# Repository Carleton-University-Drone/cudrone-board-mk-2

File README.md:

# cudrone-board-mk-2
This is the second iteration of the drone's main flight controller. The main processor for this board is an intel edison.

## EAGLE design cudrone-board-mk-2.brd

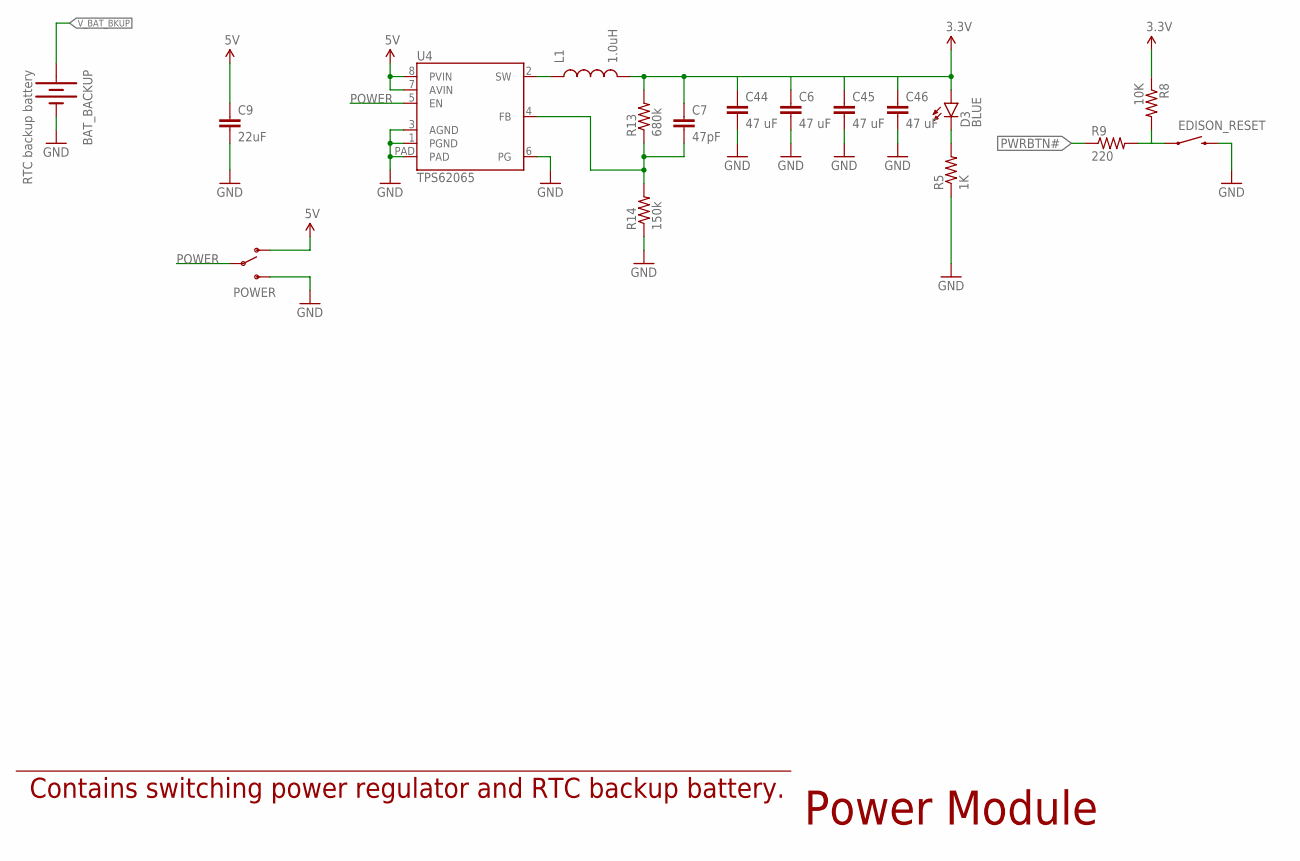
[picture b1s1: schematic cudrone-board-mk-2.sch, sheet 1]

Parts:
BAT_BACKUP: RTC backup battery; BATTCON_12MM
C6, C44, C45, C46: 47 uF; 0805
C7: 47pF; 0603-CAP
C9: 22uF; 0805
D3: BLUE; LED-0603
EDISON_RESET: SWITCH-MOMENTARY-2; EVQPSC02K
L1: 1.0uH; INDUCTOR-SRP4020
POWER: CANSAT_SWITCH; JS102011SAQN-SPDT
R5: 1K; 0603-RES@1
R8: 10K; 0603-RES@1
R9: 220; 0603-RES@1
R13: 680k; 0603-RES
R14: 150k; 0603-RES
U4: TPS62065; WSON-8-PAD

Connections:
3.3V: C6.1, C7.1, C44.1, C45.1, C46.1, D3.A, L1.P$2 (2), R8.1, R13.2; also elsewhere on the board
5V: C9.1, POWER.P$1 (O), U4.7 (AVIN), U4.8 (PVIN); also elsewhere on the board
GND: BAT_BACKUP.GND (-), C6.2, C9.2, C44.2, C45.2, C46.2, EDISON_RESET.B (2), EDISON_RESET.B' (2), POWER.P$3 (S), R5.1, R14.1, U4.1 (PGND), U4.3 (AGND), U4.6 (PG), U4.PAD; also elsewhere on the board
unnamed: D3.C, R5.2
unnamed: EDISON_RESET.A (1), EDISON_RESET.A' (1), R8.2, R9.2
unnamed: C7.2, R13.1, R14.2, U4.4 (FB)
unnamed: L1.P$1 (1), U4.2 (SW)
POWER: POWER.P$C, U4.5 (EN)
PWRBTN#: R9.1; also elsewhere on the board
V_BAT_BKUP: BAT_BACKUP.PWR@1 (+); also elsewhere on the board

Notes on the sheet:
Power Module
Contains switching power regulator and RTC backup battery.

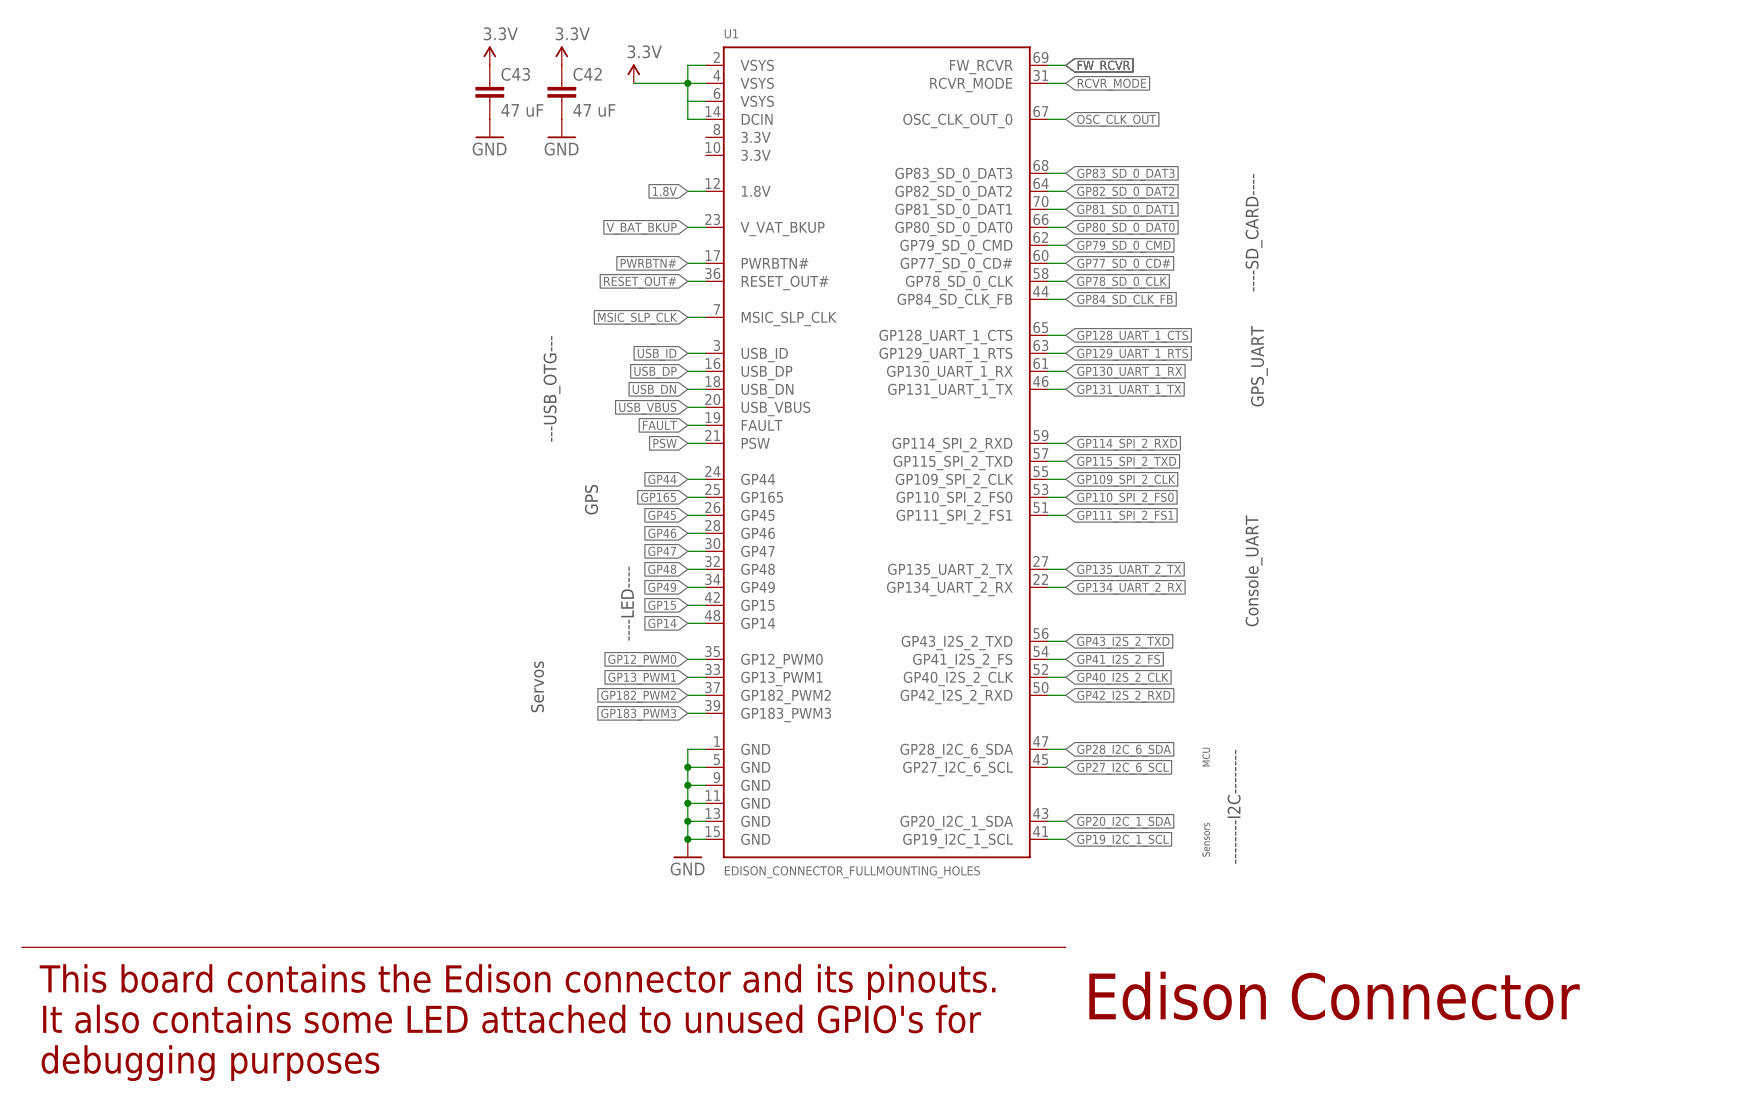
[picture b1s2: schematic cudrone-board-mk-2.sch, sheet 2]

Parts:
C42, C43: 47 uF; 0805
U1: EDISON_CONNECTOR_FULLMOUNTING_HOLES; EDISON_DAUGHTER

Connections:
1.8V: U1.12 (1.8V); also elsewhere on the board
3.3V: C42.1, C43.1, U1.2 (VSYS), U1.4 (VSYS), U1.6 (VSYS), U1.14 (DCIN); also elsewhere on the board
FAULT: U1.19 (FAULT); also elsewhere on the board
FW_RCVR: U1.69 (FW_RCVR)
GND: C42.2, C43.2, U1.1 (GND), U1.5 (GND), U1.9 (GND), U1.11 (GND), U1.13 (GND), U1.15 (GND); also elsewhere on the board
GP12_PWM0: U1.35 (GP12_PWM0); also elsewhere on the board
GP13_PWM1: U1.33 (GP13_PWM1); also elsewhere on the board
GP14: U1.48 (GP14)
GP15: U1.42 (GP15)
GP19_I2C_1_SCL: U1.41 (GP19_I2C_1_SCL); also elsewhere on the board
GP20_I2C_1_SDA: U1.43 (GP20_I2C_1_SDA); also elsewhere on the board
GP27_I2C_6_SCL: U1.45 (GP27_I2C_6_SCL); also elsewhere on the board
GP28_I2C_6_SDA: U1.47 (GP28_I2C_6_SDA); also elsewhere on the board
GP40_I2S_2_CLK: U1.52 (GP40_I2S_2_CLK)
GP41_I2S_2_FS: U1.54 (GP41_I2S_2_FS)
GP42_I2S_2_RXD: U1.50 (GP42_I2S_2_RXD)
GP43_I2S_2_TXD: U1.56 (GP43_I2S_2_TXD)
GP44: U1.24 (GP44); also elsewhere on the board
GP45: U1.26 (GP45); also elsewhere on the board
GP46: U1.28 (GP46)
GP47: U1.30 (GP47)
GP48: U1.32 (GP48)
GP49: U1.34 (GP49)
GP77_SD_0_CD#: U1.60 (GP77_SD_0_CD#); also elsewhere on the board
GP78_SD_0_CLK: U1.58 (GP78_SD_0_CLK); also elsewhere on the board
GP79_SD_0_CMD: U1.62 (GP79_SD_0_CMD); also elsewhere on the board
GP80_SD_0_DAT0: U1.66 (GP80_SD_0_DAT0); also elsewhere on the board
GP81_SD_0_DAT1: U1.70 (GP81_SD_0_DAT1); also elsewhere on the board
GP82_SD_0_DAT2: U1.64 (GP82_SD_0_DAT2); also elsewhere on the board
GP83_SD_0_DAT3: U1.68 (GP83_SD_0_DAT3); also elsewhere on the board
GP84_SD_CLK_FB: U1.44 (GP84_SD_CLK_FB); also elsewhere on the board
GP109_SPI_2_CLK: U1.55 (GP109_SPI_2_CLK)
GP110_SPI_2_FS0: U1.53 (GP110_SPI_2_FS0)
GP111_SPI_2_FS1: U1.51 (GP111_SPI_2_FS1)
GP114_SPI_2_RXD: U1.59 (GP114_SPI_2_RXD)
GP115_SPI_2_TXD: U1.57 (GP115_SPI_2_TXD)
GP128_UART_1_CTS: U1.65 (GP128_UART_1_CTS)
GP129_UART_1_RTS: U1.63 (GP129_UART_1_RTS)
GP130_UART_1_RX: U1.61 (GP130_UART_1_RX); also elsewhere on the board
GP131_UART_1_TX: U1.46 (GP131_UART_1_TX); also elsewhere on the board
GP134_UART_2_RX: U1.22 (GP134_UART_2_RX); also elsewhere on the board
GP135_UART_2_TX: U1.27 (GP135_UART_2_TX); also elsewhere on the board
GP165: U1.25 (GP165); also elsewhere on the board
GP182_PWM2: U1.37 (GP182_PWM2); also elsewhere on the board
GP183_PWM3: U1.39 (GP183_PWM3); also elsewhere on the board
MSIC_SLP_CLK: U1.7 (MSIC_SLP_CLK)
OSC_CLK_OUT: U1.67 (OSC_CLK_OUT_0)
PSW: U1.21 (PSW); also elsewhere on the board
PWRBTN#: U1.17 (PWRBTN#); also elsewhere on the board
RCVR_MODE: U1.31 (RCVR_MODE)
RESET_OUT#: U1.36 (RESET_OUT#)
USB_DN: U1.18 (USB_DN); also elsewhere on the board
USB_DP: U1.16 (USB_DP); also elsewhere on the board
USB_ID: U1.3 (USB_ID); also elsewhere on the board
USB_VBUS: U1.20 (USB_VBUS); also elsewhere on the board
V_BAT_BKUP: U1.23 (V_VAT_BKUP); also elsewhere on the board

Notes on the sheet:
Edison Connector
This board contains the Edison connector and its pinouts. It also contains some LED attached to unused GPIO's for debugging purposes
Servos
GPS
Console_UART
---USB_OTG---
----SD_CARD----
--------I2C--------
GPS_UART
Sensors
MCU
----LED----

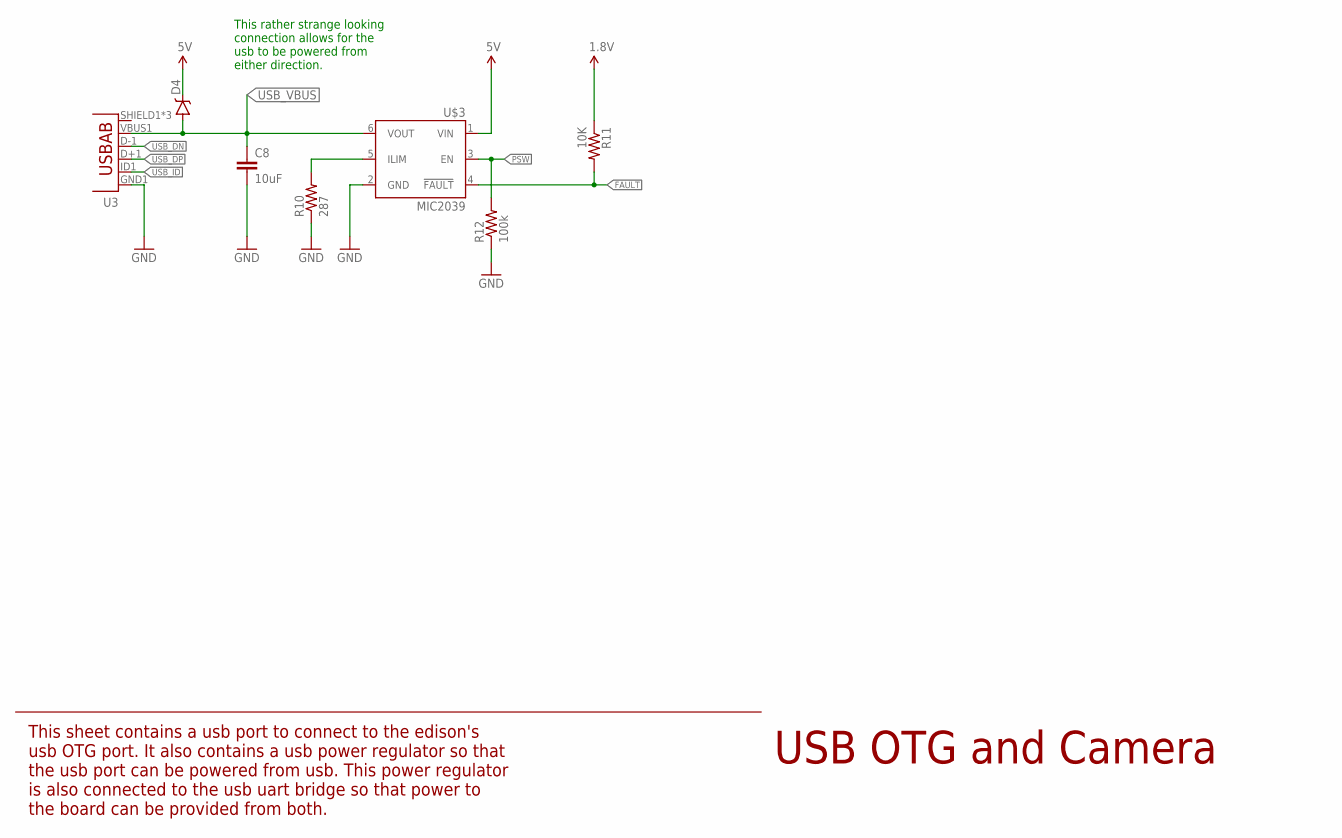
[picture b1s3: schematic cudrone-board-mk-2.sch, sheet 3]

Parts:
C8: 10uF; 1206
D4: DIODE-SCHOTTKY-MBRA140; SMA-DIODE
R10: 287; 0603-RES@1
R11: 10K; 0603-RES@1
R12: 100k; 0603-RES@1
U3: USB-ABCONN-11794; USB-AB-MICRO-SMD_V03
U$3: MIC2039; SOT23-6

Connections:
1.8V: R11.1; also elsewhere on the board
5V: D4.C, U$3.1 (VIN); also elsewhere on the board
FAULT: R11.2, U$3.4 (!FAULT); also elsewhere on the board
GND: C8.2, R10.1, R12.1, U3.GND1 (GND), U$3.2 (GND); also elsewhere on the board
unnamed: R10.2, U$3.5 (ILIM)
PSW: R12.2, U$3.3 (EN); also elsewhere on the board
USB_DN: U3.D-1 (D-); also elsewhere on the board
USB_DP: U3.D+1 (D+); also elsewhere on the board
USB_ID: U3.ID1 (USBID); also elsewhere on the board
USB_VBUS: C8.1, D4.A, U3.VBUS1 (VBUS), U$3.6 (VOUT); also elsewhere on the board

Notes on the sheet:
USB OTG and Camera
This sheet contains a usb port to connect to the edison's usb OTG port. It also contains a usb power regulator so that the usb port can be powered from usb. This power regulator is also connected to the usb uart bridge so that power to the board can be provided from both.
This rather strange looking connection allows for the usb to be powered from either direction.

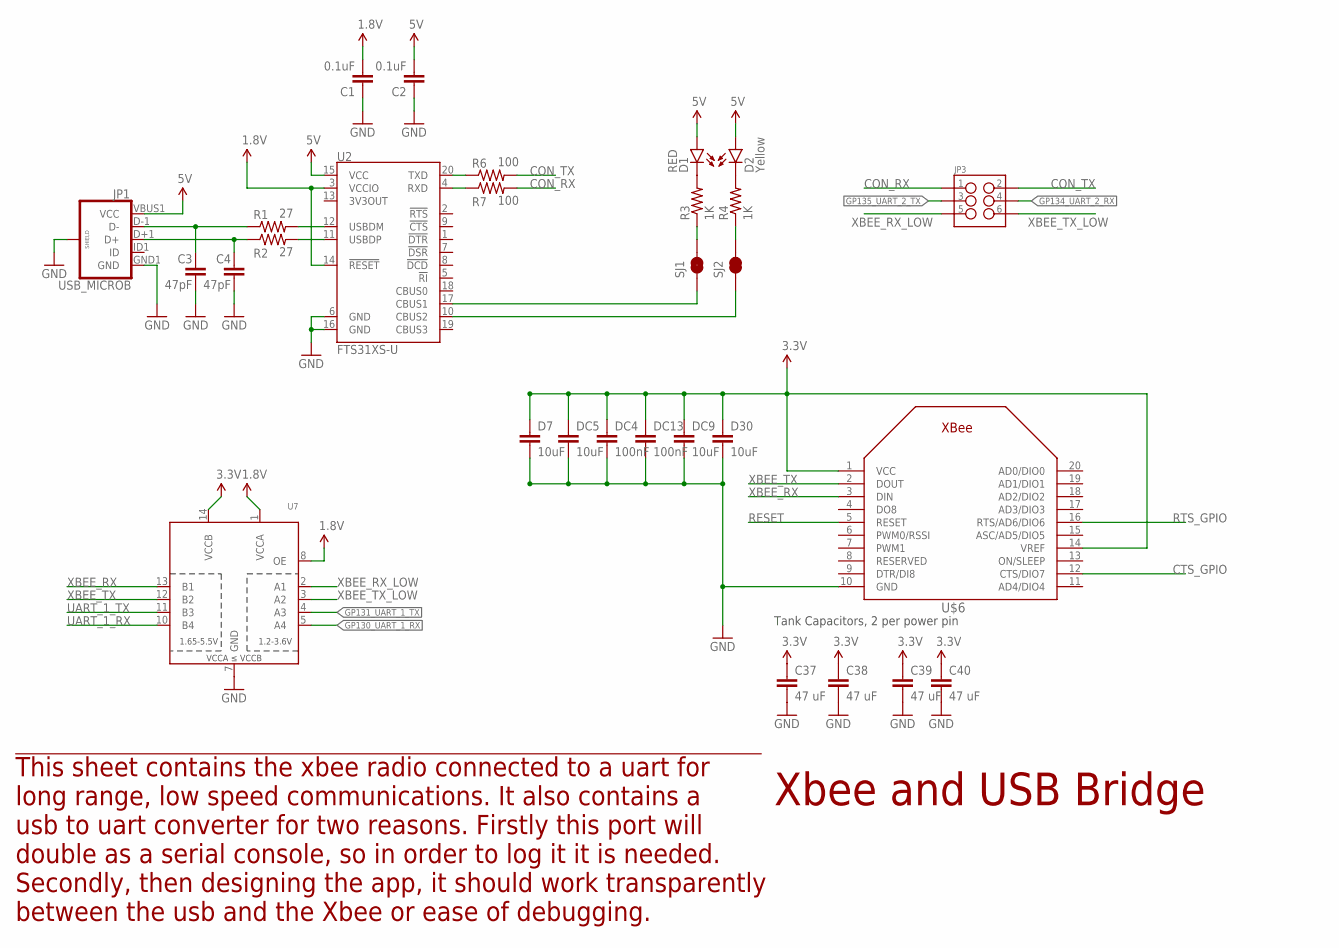
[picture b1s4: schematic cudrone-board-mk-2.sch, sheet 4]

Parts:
C1, C2: 0.1uF; 0603-CAP
C3, C4: 47pF; 0603-CAP
C37, C38, C39, C40: 47 uF; 0805
D1: RED; LED-0603
D2: Yellow; LED-0603
D7, D30: 10uF; 0603-CAP
DC4, DC13: 100nF; 0603-CAP
DC5, DC9: 10uF; 0603-CAP
JP1: USB_MICROB; USB-B-MICRO-SMD_V03
JP3: M03X2DOUBLE_JUMPER_SWAP; 2X3-DOUBLE-JUMPER-SWAP
R1, R2: 27; 0603
R3, R4: 1K; 0603-RES@1
R6, R7: 100; 0603-RES@1
SJ1, SJ2: JUMPER-PAD-2-NC_BY_TRACE; PAD-JUMPER-2-NC_BY_TRACE_YES_SILK
U2: FTS31XS-U; SSOP20_L
U7: TXB0104PWRSOIC14; SO14
U$6: XBEE

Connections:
1.8V: C1.2, U2.3 (VCCIO), U2.14 (!RESET), U7.1 (VCCA), U7.8 (OE); also elsewhere on the board
3.3V: C37.1, C38.1, C39.1, C40.1, D7.1, D30.1, DC4.1, DC5.1, DC9.1, DC13.1, U7.14 (VCCB), U$6.1 (VCC), U$6.14 (VREF); also elsewhere on the board
5V: C2.2, D1.A, D2.A, JP1.VBUS1 (VCC), U2.15 (VCC); also elsewhere on the board
CON_RX: JP3.1, R7.2
CON_TX: JP3.2, R6.2
CTS_GPIO: U$6.12 (CTS/DIO7)
GND: C1.1, C2.1, C3.2, C4.2, C37.2, C38.2, C39.2, C40.2, D7.2, D30.2, DC4.2, DC5.2, DC9.2, DC13.2, JP1.GND1 (GND), JP1.SHIELD1 (SHIELD), JP1.SHIELD2 (SHIELD), JP1.SHIELD3 (SHIELD), U2.6 (GND), U2.16 (GND), U7.7 (GND), U$6.10 (GND); also elsewhere on the board
GP130_UART_1_RX: U7.5 (A4); also elsewhere on the board
GP131_UART_1_TX: U7.4 (A3); also elsewhere on the board
GP134_UART_2_RX: JP3.4; also elsewhere on the board
GP135_UART_2_TX: JP3.3; also elsewhere on the board
unnamed: SJ1.1, U2.17 (CBUS1)
unnamed: C3.1, JP1.D-1 (D-), R1.1
unnamed: C4.1, JP1.D+1 (D+), R2.1
unnamed: R1.2, U2.12 (USBDM)
unnamed: R2.2, U2.11 (USBDP)
unnamed: SJ2.1, U2.10 (CBUS2)
unnamed: R3.1, SJ1.2
unnamed: R4.1, SJ2.2
unnamed: D1.C, R3.2
unnamed: D2.C, R4.2
unnamed: R6.1, U2.20 (TXD)
unnamed: R7.1, U2.4 (RXD)
RESET: U$6.5 (RESET)
RTS_GPIO: U$6.16 (RTS/AD6/DIO6)
UART_1_RX: U7.10 (B4)
UART_1_TX: U7.11 (B3); also elsewhere on the board
XBEE_RX: U7.13 (B1), U$6.3 (DIN)
XBEE_RX_LOW: JP3.5, U7.2 (A1)
XBEE_TX: U7.12 (B2), U$6.2 (DOUT)
XBEE_TX_LOW: JP3.6, U7.3 (A2)

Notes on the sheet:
Xbee and USB Bridge
This sheet contains the xbee radio connected to a uart for long range, low speed communications. It also contains a usb to uart converter for two reasons. Firstly this port will double as a serial console, so in order to log it it is needed. Secondly, then designing the app, it should work transpar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
Tank Capacitors, 2 per power pin

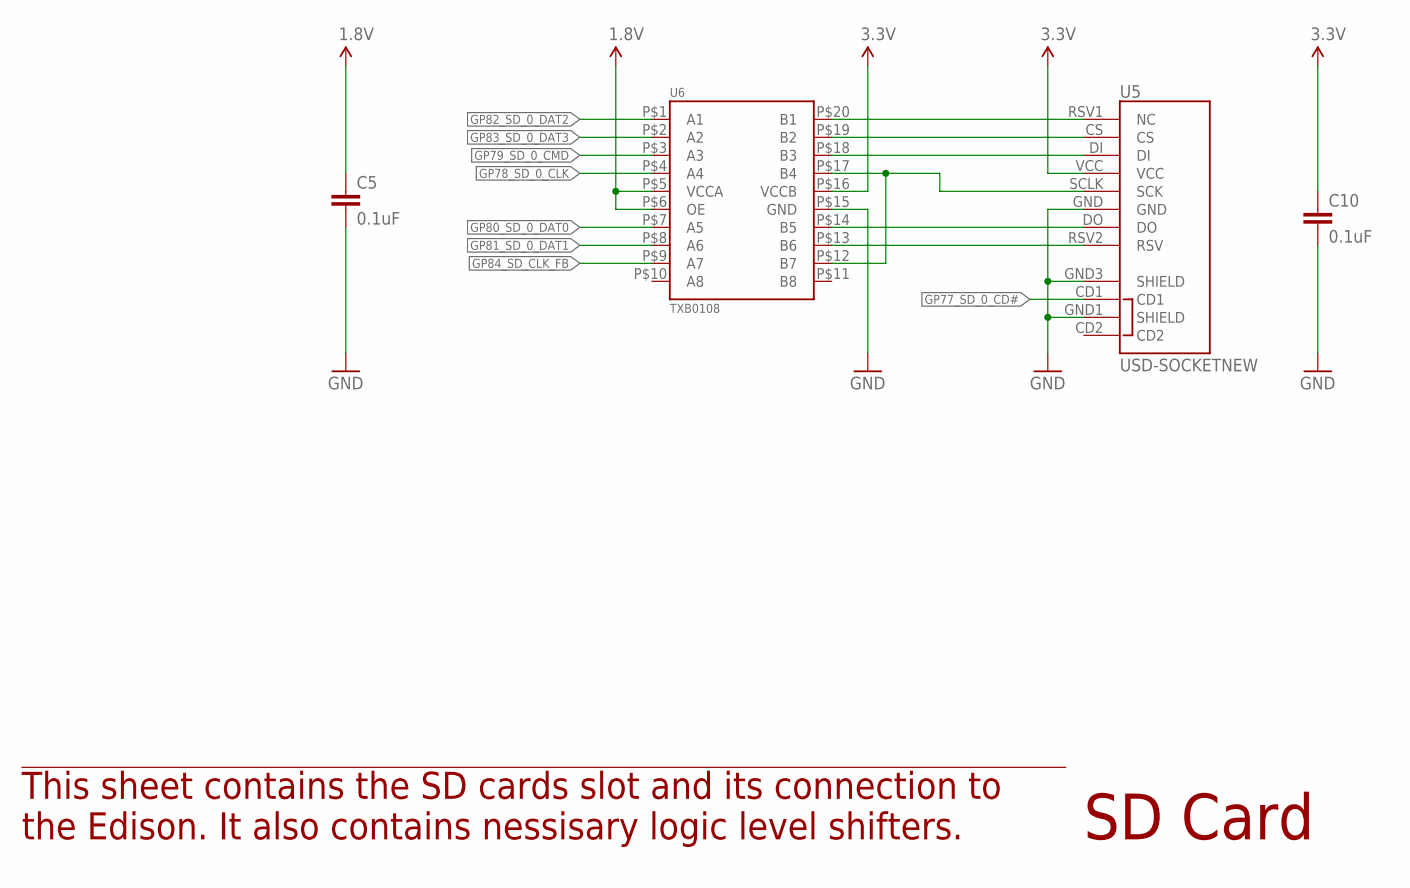
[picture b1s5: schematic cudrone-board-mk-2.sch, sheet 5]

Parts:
C5, C10: 0.1uF; 0603-CAP
U5: USD-SOCKETNEW; MICRO-SD-SOCKET-PP
U6: TXB0108; UFDFN-20

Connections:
1.8V: C5.1, U6.P$5 (VCCA), U6.P$6 (OE); also elsewhere on the board
3.3V: C10.1, U5.VCC, U6.P$16 (VCCB); also elsewhere on the board
GND: C5.2, C10.2, U5.GND, U5.GND1 (SHIELD), U5.GND3 (SHIELD), U6.P$15 (GND); also elsewhere on the board
GP77_SD_0_CD#: U5.CD1; also elsewhere on the board
GP78_SD_0_CLK: U6.P$4 (A4); also elsewhere on the board
GP79_SD_0_CMD: U6.P$3 (A3); also elsewhere on the board
GP80_SD_0_DAT0: U6.P$7 (A5); also elsewhere on the board
GP81_SD_0_DAT1: U6.P$8 (A6); also elsewhere on the board
GP82_SD_0_DAT2: U6.P$1 (A1); also elsewhere on the board
GP83_SD_0_DAT3: U6.P$2 (A2); also elsewhere on the board
GP84_SD_CLK_FB: U6.P$9 (A7); also elsewhere on the board
unnamed: U5.RSV1 (NC), U6.P$20 (B1)
unnamed: U5.CS, U6.P$19 (B2)
unnamed: U5.DI, U6.P$18 (B3)
unnamed: U5.DO, U6.P$14 (B5)
unnamed: U5.RSV2 (RSV), U6.P$13 (B6)
SCK: U5.SCLK (SCK), U6.P$12 (B7), U6.P$17 (B4)

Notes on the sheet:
SD Card
This sheet contains the SD cards slot and its connection to the Edison. It also contains nessisary logic level shifters.

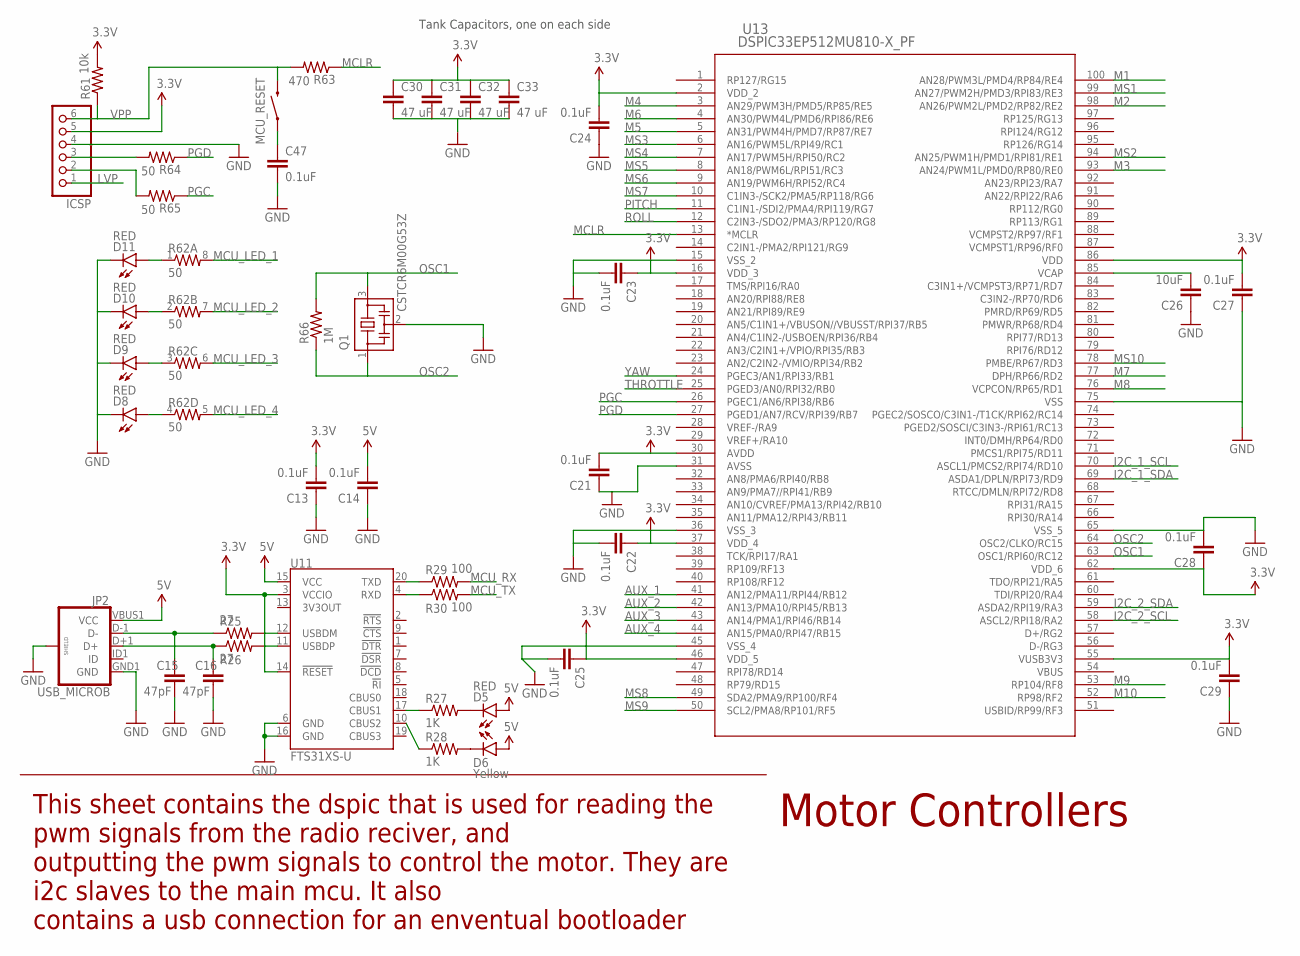
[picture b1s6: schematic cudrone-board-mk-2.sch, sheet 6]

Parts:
C13, C14, C21, C22, C23, C24, C25, C27, C28, C29, C47: 0.1uF; 0603-CAP
C15, C16: 47pF; 0603-CAP
C26: 10uF; 0603-CAP
C30, C31, C32, C33: 47 uF; 0805
D5, D8, D9, D10, D11: RED; LED-0603
D6: Yellow; LED-0603
ICSP: PINHD-1X6/90; 1X06/90
JP2: USB_MICROB; USB-B-MICRO-SMD_V03
MCU_RESET: SWITCH-MOMENTARY-2; EVQPSC02K
Q1: CSTCR6M00G53Z; CSTCR6M
R25, R26: 27; 0603
R27, R28: 1K; 0603-RES@1
R29, R30: 100; 0603-RES@1
R61: 10k; 0603
R62: 50; 0603-ARV
R63: 470; 0603
R64, R65: 50; 0603
R66: 1M; 0603
U11: FTS31XS-U; SSOP20_L
U13: DSPIC33EP512MU810-X_PF; TQFP100_14X14MC

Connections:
3.3V: C13.2, C21.2, C22.1, C23.1, C24.2, C25.1, C27.2, C28.1, C29.2, C30.1, C31.1, C32.1, C33.1, ICSP.5, R61.2, U11.3 (VCCIO), U11.14 (!RESET), U13.2 (VDD_2), U13.16 (VDD_3), U13.30 (AVDD), U13.37 (VDD_4), U13.46 (VDD_5), U13.55 (VUSB3V3), U13.62 (VDD_6), U13.86 (VDD); also elsewhere on the board
5V: C14.2, D5.A, D6.A, JP2.VBUS1 (VCC), U11.15 (VCC); also elsewhere on the board
AUX_1: U13.41 (AN12/PMA11/RPI44/RB12); also elsewhere on the board
AUX_2: U13.42 (AN13/PMA10/RPI45/RB13); also elsewhere on the board
AUX_3: U13.43 (AN14/PMA1/RPI46/RB14); also elsewhere on the board
AUX_4: U13.44 (AN15/PMA0/RPI47/RB15); also elsewhere on the board
GND: C13.1, C14.1, C15.2, C16.2, C21.1, C22.2, C23.2, C24.1, C25.2, C26.1, C27.1, C28.2, C29.1, C30.2, C31.2, C32.2, C33.2, C47.2, D8.C, D9.C, D10.C, D11.C, ICSP.4, JP2.GND1 (GND), JP2.SHIELD1 (SHIELD), JP2.SHIELD2 (SHIELD), JP2.SHIELD3 (SHIELD), Q1.2, U11.6 (GND), U11.16 (GND), U13.15 (VSS_2), U13.31 (AVSS), U13.36 (VSS_3), U13.45 (VSS_4), U13.65 (VSS_5), U13.75 (VSS); also elsewhere on the board
I2C_1_SCL: U13.70 (ASCL1/PMCS2/RPI74/RD10); also elsewhere on the board
I2C_1_SDA: U13.69 (ASDA1/DPLN/RPI73/RD9); also elsewhere on the board
I2C_2_SCL: U13.58 (ASCL2/RPI18/RA2); also elsewhere on the board
I2C_2_SDA: U13.59 (ASDA2/RPI19/RA3); also elsewhere on the board
LVP: ICSP.1
M1: U13.100 (AN28/PWM3L/PMD4/RP84/RE4); also elsewhere on the board
M2: U13.98 (AN26/PWM2L/PMD2/RP82/RE2); also elsewhere on the board
M3: U13.93 (AN24/PWM1L/PMD0/RP80/RE0); also elsewhere on the board
M4: U13.3 (AN29/PWM3H/PMD5/RP85/RE5); also elsewhere on the board
M5: U13.5 (AN31/PWM4H/PMD7/RP87/RE7); also elsewhere on the board
M6: U13.4 (AN30/PWM4L/PMD6/RPI86/RE6); also elsewhere on the board
M7: U13.77 (DPH/RP66/RD2); also elsewhere on the board
M8: U13.76 (VCPCON/RP65/RD1); also elsewhere on the board
M9: U13.53 (RP104/RF8); also elsewhere on the board
M10: U13.52 (RP98/RF2); also elsewhere on the board
MCLR: R63.1, U13.13 (*MCLR)
MCU_LED_1: R62.8 (2)
MCU_LED_2: R62.7 (2)
MCU_LED_3: R62.6 (2)
MCU_LED_4: R62.5 (2)
MCU_RX: R29.2
MCU_TX: R30.2
MS1: U13.99 (AN27/PWM2H/PMD3/RPI83/RE3); also elsewhere on the board
MS2: U13.94 (AN25/PWM1H/PMD1/RPI81/RE1); also elsewhere on the board
MS3: U13.6 (AN16/PWM5L/RPI49/RC1); also elsewhere on the board
MS4: U13.7 (AN17/PWM5H/RPI50/RC2); also elsewhere on the board
MS5: U13.8 (AN18/PWM6L/RPI51/RC3); also elsewhere on the board
MS6: U13.9 (AN19/PWM6H/RPI52/RC4); also elsewhere on the board
MS7: U13.10 (C1IN3-/SCK2/PMA5/RP118/RG6); also elsewhere on the board
MS8: U13.49 (SDA2/PMA9/RP100/RF4); also elsewhere on the board
MS9: U13.50 (SCL2/PMA8/RP101/RF5); also elsewhere on the board
MS10: U13.78 (PMBE/RP67/RD3); also elsewhere on the board
unnamed: D8.A, R62.4 (1)
unnamed: C15.1, JP2.D-1 (D-), R25.1
unnamed: C16.1, JP2.D+1 (D+), R26.1
unnamed: R25.2, U11.12 (USBDM)
unnamed: R26.2, U11.11 (USBDP)
unnamed: C26.2, U13.85 (VCAP)
unnamed: R28.1, U11.10 (CBUS2)
unnamed: R27.1, U11.17 (CBUS1)
unnamed: D9.A, R62.3 (1)
unnamed: D5.C, R27.2
unnamed: D6.C, R28.2
unnamed: R29.1, U11.20 (TXD)
unnamed: R30.1, U11.4 (RXD)
unnamed: D10.A, R62.2 (1)
unnamed: D11.A, R62.1
unnamed: C47.1, MCU_RESET.A (1), MCU_RESET.A' (1)
unnamed: ICSP.3, R64.2
unnamed: ICSP.2, R65.2
OSC1: Q1.3, R66.2, U13.63 (OSC1/RPI60/RC12)
OSC2: Q1.1, R66.1, U13.64 (OSC2/CLKO/RC15)
PGC: R65.1, U13.26 (PGEC1/AN6/RPI38/RB6)
PGD: R64.1, U13.27 (PGED1/AN7/RCV/RPI39/RB7)
PITCH: U13.11 (C1IN1-/SDI2/PMA4/RPI119/RG7); also elsewhere on the board
ROLL: U13.12 (C2IN3-/SDO2/PMA3/RP120/RG8); also elsewhere on the board
THROTTLE: U13.25 (PGED3/AN0/RPI32/RB0); also elsewhere on the board
VBUS: U13.54 (VBUS)
VPP: ICSP.6, MCU_RESET.B (2), MCU_RESET.B' (2), R61.1, R63.2
YAW: U13.24 (PGEC3/AN1/RPI33/RB1); also elsewhere on the board

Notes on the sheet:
Motor Controllers
This sheet contains the dspic that is used for reading the pwm signals from the radio reciver, and outputting the pwm signals to control the motor. They are i2c slaves to the main mcu. It also contains a usb connection for an enventual bootloader
Tank Capacitors, one on each side

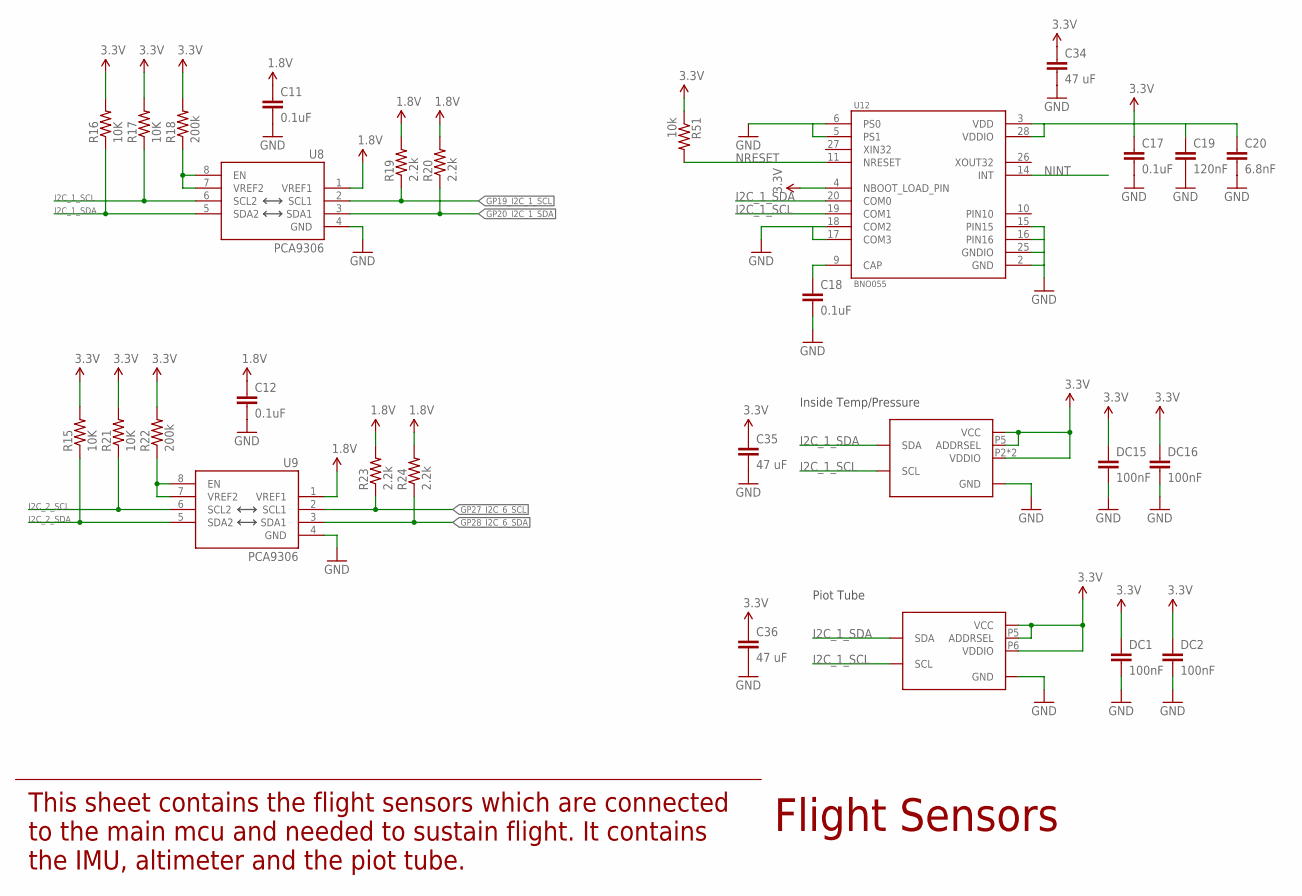
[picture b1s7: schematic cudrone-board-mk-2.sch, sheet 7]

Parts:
C11, C12, C17, C18: 0.1uF; 0603-CAP
C19: 120nF; 0603-CAP
C20: 6.8nF; 0603-CAP
C34, C35, C36: 47 uF; 0805
DC1, DC2, DC15, DC16: 100nF; 0603-CAP
R15, R16, R17, R21: 10K; 0603-RES@1
R18, R22: 200k; 0603-RES@1
R19, R20, R23, R24: 2.2k; 0603-RES@1
R51: 10k; 0805
U8, U9: PCA9306; PCA9306DC-1:1
U12: BNO055; LGA28R50P4X10_380X520X100
U$4: BMP280; LGA-8
U$5: BMP280PITOT; BMP280_PITOT

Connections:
1.8V: C11.1, C12.1, R19.2, R20.2, R23.2, R24.2, U8.1 (VREF1), U9.1 (VREF1); also elsewhere on the board
3.3V: C17.1, C19.1, C20.1, C34.1, C35.1, C36.1, DC1.1, DC2.1, DC15.1, DC16.1, R15.2, R16.2, R17.2, R18.2, R21.2, R22.2, R51.1, U12.3 (VDD), U12.4 (NBOOT_LOAD_PIN), U12.28 (VDDIO), U$4.P2 (VDDIO), U$4.P5 (ADDRSEL), U$4.P6 (VDDIO), U$4.P8 (VCC), U$5.P2 (VCC), U$5.P5 (ADDRSEL), U$5.P6 (VDDIO), U$5.P8 (VCC); also elsewhere on the board
GND: C11.2, C12.2, C17.2, C18.2, C19.2, C20.2, C34.2, C35.2, C36.2, DC1.2, DC2.2, DC15.2, DC16.2, U8.4 (GND), U9.4 (GND), U12.2 (GND), U12.5 (PS1), U12.6 (PS0), U12.15 (PIN15), U12.16 (PIN16), U12.17 (COM3), U12.18 (COM2), U12.25 (GNDIO), U$4.P1 (GND), U$4.P7 (GND), U$5.P1 (GND), U$5.P7 (GND); also elsewhere on the board
GP19_I2C_1_SCL: R19.1, U8.2 (SCL1); also elsewhere on the board
GP20_I2C_1_SDA: R20.1, U8.3 (SDA1); also elsewhere on the board
GP27_I2C_6_SCL: R23.1, U9.2 (SCL1); also elsewhere on the board
GP28_I2C_6_SDA: R24.1, U9.3 (SDA1); also elsewhere on the board
I2C_1_SCL: R17.1, U8.6 (SCL2), U12.19 (COM1), U$4.P4 (SCL), U$5.P4 (SCL); also elsewhere on the board
I2C_1_SDA: R16.1, U8.5 (SDA2), U12.20 (COM0), U$4.P3 (SDA), U$5.P3 (SDA); also elsewhere on the board
I2C_2_SCL: R21.1, U9.6 (SCL2); also elsewhere on the board
I2C_2_SDA: R15.1, U9.5 (SDA2); also elsewhere on the board
unnamed: R22.1, U9.7 (VREF2), U9.8 (EN)
unnamed: R18.1, U8.7 (VREF2), U8.8 (EN)
unnamed: C18.1, U12.9 (CAP)
NINT: U12.14 (INT)
NRESET: R51.2, U12.11 (NRESET)
PIN10: U12.10 (PIN10)

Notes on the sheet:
Flight Sensors
This sheet contains the flight sensors which are connected to the main mcu and needed to sustain flight. It contains the IMU, altimeter and the piot tube.
Inside Temp/Pressure
Piot Tube

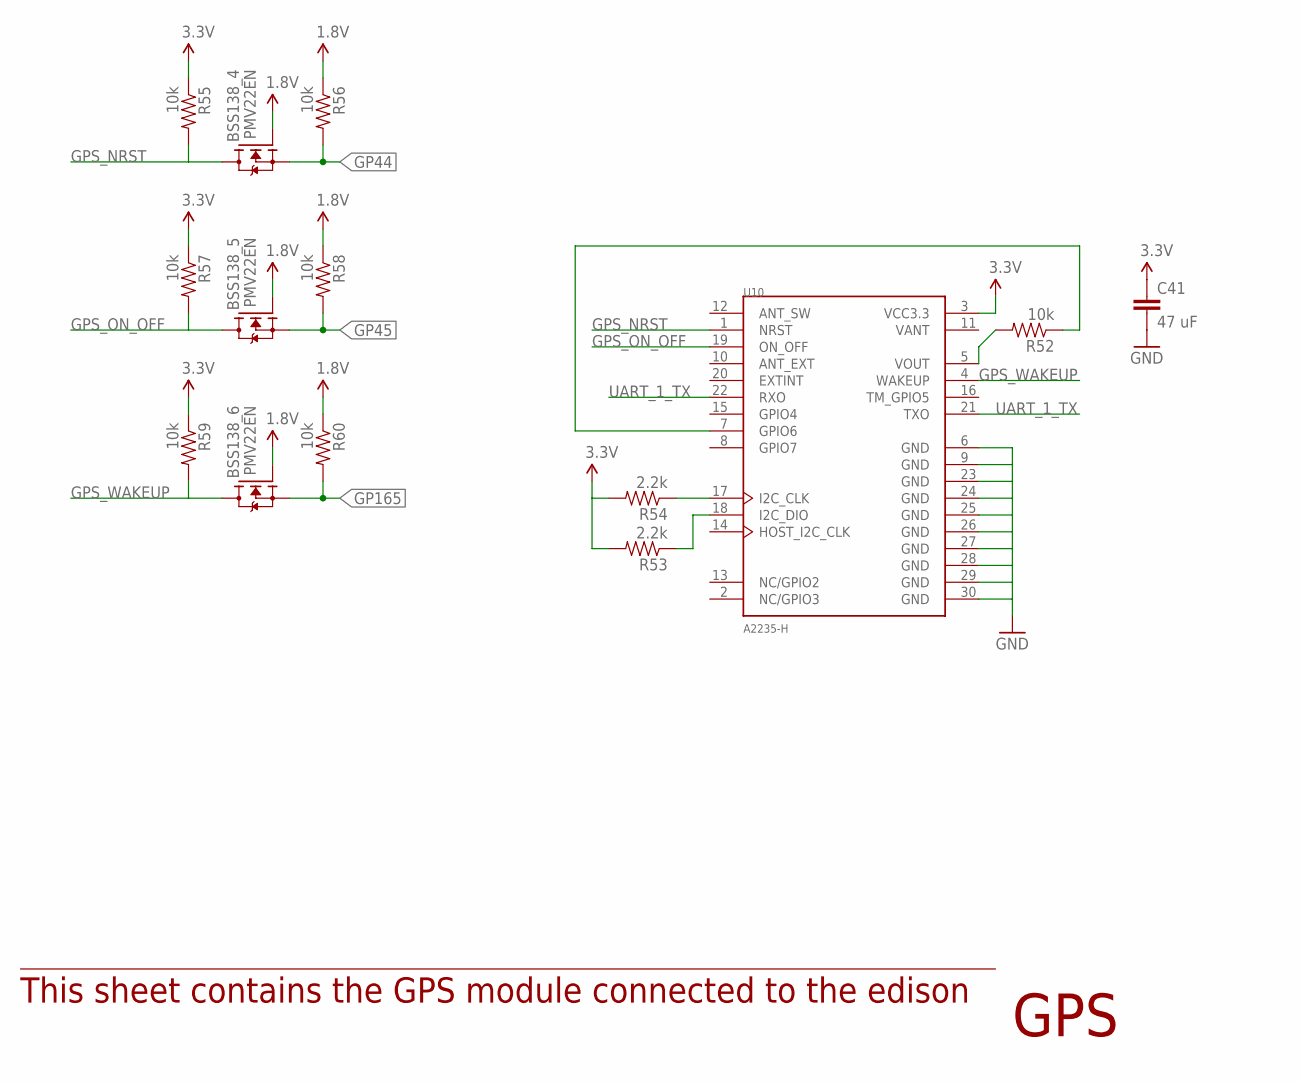
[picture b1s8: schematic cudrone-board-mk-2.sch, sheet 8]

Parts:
BSS138_4, BSS138_5, BSS138_6: PMV22EN; SOT23
C41: 47 uF; 0805
R52: 10k; 0603-RES@1
R53, R54: 2.2k; 0603-RES@1
R55, R56, R57, R58, R59, R60: 10k; 0805
U10: A2235-H; XCVR_A2235-H

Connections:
1.8V: BSS138_4.1 (G), BSS138_5.1 (G), BSS138_6.1 (G), R56.1, R58.1, R60.1; also elsewhere on the board
3.3V: C41.1, R53.2, R54.2, R55.1, R57.1, R59.1, U10.3 (VCC3.3); also elsewhere on the board
GND: C41.2, U10.6 (GND), U10.9 (GND), U10.23 (GND), U10.24 (GND), U10.25 (GND), U10.26 (GND), U10.27 (GND), U10.28 (GND), U10.29 (GND), U10.30 (GND); also elsewhere on the board
GP44: BSS138_4.2 (S), R56.2; also elsewhere on the board
GP45: BSS138_5.2 (S), R58.2; also elsewhere on the board
GP165: BSS138_6.2 (S), R60.2; also elsewhere on the board
GPS_NRST: BSS138_4.3 (D), R55.2, U10.1 (NRST)
GPS_ON_OFF: BSS138_5.3 (D), R57.2, U10.19 (ON_OFF)
GPS_WAKEUP: BSS138_6.3 (D), R59.2, U10.4 (WAKEUP)
unnamed: R52.1, U10.7 (GPIO6)
unnamed: R52.2, U10.5 (VOUT)
unnamed: R53.1, U10.18 (I2C_DIO)
unnamed: R54.1, U10.17 (I2C_CLK)
UART_1_TX: U10.21 (TXO), U10.22 (RXO); also elsewhere on the board
VANT: U10.11 (VANT)

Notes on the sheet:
GPS
This sheet contains the GPS module connected to the edison

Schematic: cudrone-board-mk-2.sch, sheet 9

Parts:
BSS138_1, BSS138_2, BSS138_3, BSS138_7: PMV22EN; SOT23
ESC: 3X10
GIMBAL_SERVOS: 3X4
MOTOR_SERVO: 3X10
R31, R32, R33, R34, R35, R36, R37, R38, R39, R40, R41, R42: RESISTOR0603-RES; 0603-RES
R43, R44, R45, R46, R47, R48, R49, R50: 10k; 0805
RECIVER: 3X8

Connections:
1.8V: BSS138_1.1 (G), BSS138_2.1 (G), BSS138_3.1 (G), BSS138_7.1 (G), R44.1, R46.1, R48.1, R50.1; also elsewhere on the board
5V: ESC.V1 (V), ESC.V2 (V), ESC.V3 (V), ESC.V4 (V), ESC.V5 (V), ESC.V6 (V), ESC.V7 (V), ESC.V8 (V), ESC.V9 (V), ESC.V10 (V), GIMBAL_SERVOS.V1 (V), GIMBAL_SERVOS.V2 (V), GIMBAL_SERVOS.V3 (V), GIMBAL_SERVOS.V4 (V), MOTOR_SERVO.V1 (V), MOTOR_SERVO.V2 (V), MOTOR_SERVO.V3 (V), MOTOR_SERVO.V4 (V), MOTOR_SERVO.V5 (V), MOTOR_SERVO.V6 (V), MOTOR_SERVO.V7 (V), MOTOR_SERVO.V8 (V), MOTOR_SERVO.V9 (V), MOTOR_SERVO.V10 (V), R31.2, R32.2, R33.2, R34.2, R35.2, R36.2, R37.2, R38.2, R39.2, R40.2, R41.2, R42.2, R43.1, R45.1, R47.1, R49.1, RECIVER.V1 (V), RECIVER.V2 (V), RECIVER.V3 (V), RECIVER.V4 (V), RECIVER.V5 (V), RECIVER.V6 (V), RECIVER.V7 (V), RECIVER.V8 (V); also elsewhere on the board
AUX_1: RECIVER.S4 (4); also elsewhere on the board
AUX_2: RECIVER.S3 (3); also elsewhere on the board
AUX_3: RECIVER.S2 (2); also elsewhere on the board
AUX_4: RECIVER.S1 (1); also elsewhere on the board
GND: ESC.G1 (G), ESC.G2 (G), ESC.G3 (G), ESC.G4 (G), ESC.G5 (G), ESC.G6 (G), ESC.G7 (G), ESC.G8 (G), ESC.G9 (G), ESC.G10 (G), GIMBAL_SERVOS.G1 (G), GIMBAL_SERVOS.G2 (G), GIMBAL_SERVOS.G3 (G), GIMBAL_SERVOS.G4 (G), MOTOR_SERVO.G1 (G), MOTOR_SERVO.G2 (G), MOTOR_SERVO.G3 (G), MOTOR_SERVO.G4 (G), MOTOR_SERVO.G5 (G), MOTOR_SERVO.G6 (G), MOTOR_SERVO.G7 (G), MOTOR_SERVO.G8 (G), MOTOR_SERVO.G9 (G), MOTOR_SERVO.G10 (G), RECIVER.G1 (G), RECIVER.G2 (G), RECIVER.G3 (G), RECIVER.G4 (G), RECIVER.G5 (G), RECIVER.G6 (G), RECIVER.G7 (G), RECIVER.G8 (G); also elsewhere on the board
GP12_PWM0: BSS138_7.2 (S), R44.2; also elsewhere on the board
GP13_PWM1: BSS138_1.2 (S), R46.2; also elsewhere on the board
GP182_PWM2: BSS138_2.2 (S), R48.2; also elsewhere on the board
GP183_PWM3: BSS138_3.2 (S), R50.2; also elsewhere on the board
GS1: BSS138_7.3 (D), GIMBAL_SERVOS.S4, R43.2
GS2: BSS138_1.3 (D), GIMBAL_SERVOS.S3, R45.2
GS3: BSS138_2.3 (D), GIMBAL_SERVOS.S2, R47.2
GS4: BSS138_3.3 (D), GIMBAL_SERVOS.S1, R49.2
M1: ESC.S10 (10), R31.1; also elsewhere on the board
M2: ESC.S9 (9), R32.1; also elsewhere on the board
M3: ESC.S8 (8), R33.1; also elsewhere on the board
M4: ESC.S7 (7), R34.1; also elsewhere on the board
M5: ESC.S6 (6), R35.1; also elsewhere on the board
M6: ESC.S5 (5), R36.1; also elsewhere on the board
M7: ESC.S4 (4); also elsewhere on the board
M8: ESC.S3 (3); also elsewhere on the board
M9: ESC.S2 (2); also elsewhere on the board
M10: ESC.S1 (1); also elsewhere on the board
MS1: MOTOR_SERVO.S10 (10), R37.1; also elsewhere on the board
MS2: MOTOR_SERVO.S9 (9), R38.1; also elsewhere on the board
MS3: MOTOR_SERVO.S8 (8), R39.1; also elsewhere on the board
MS4: MOTOR_SERVO.S7 (7), R40.1; also elsewhere on the board
MS5: MOTOR_SERVO.S6 (6), R41.1; also elsewhere on the board
MS6: MOTOR_SERVO.S5 (5), R42.1; also elsewhere on the board
MS7: MOTOR_SERVO.S4 (4); also elsewhere on the board
MS8: MOTOR_SERVO.S3 (3); also elsewhere on the board
MS9: MOTOR_SERVO.S2 (2); also elsewhere on the board
MS10: MOTOR_SERVO.S1 (1); also elsewhere on the board
PITCH: RECIVER.S8 (8); also elsewhere on the board
ROLL: RECIVER.S7 (7); also elsewhere on the board
THROTTLE: RECIVER.S5 (5); also elsewhere on the board
YAW: RECIVER.S6 (6); also elsewhere on the board

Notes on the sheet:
Connectors
This sheet contains the ports from the edison to connect to the servo motors on the gimbal and landing gear, the connections to the reciver and the connections to the esc
MCU is running at 3.3V so pullups to make output signal at 5V and the mcu is pulling down.

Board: 2 copper layers, 175 parts (0 on the bottom side), 137 nets, no tracks yet.

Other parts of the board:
U$1: LETTER_L
U$2: DOCFIELD

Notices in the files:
parts and their libraries:
SparkFun-Boards: Licensing: Creative Commons ShareAlike 4.0 International - https://creativecommons.org/licenses/by-sa/4.0
eagle-library-edeca.net-v5: This is v1 and is licensed under the Creative Commons (Attribution-Non-Commercial-Share Alike 2.0 UK)
